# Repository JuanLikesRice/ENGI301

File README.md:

# ENGI301
 Repository for ENGI301 course work

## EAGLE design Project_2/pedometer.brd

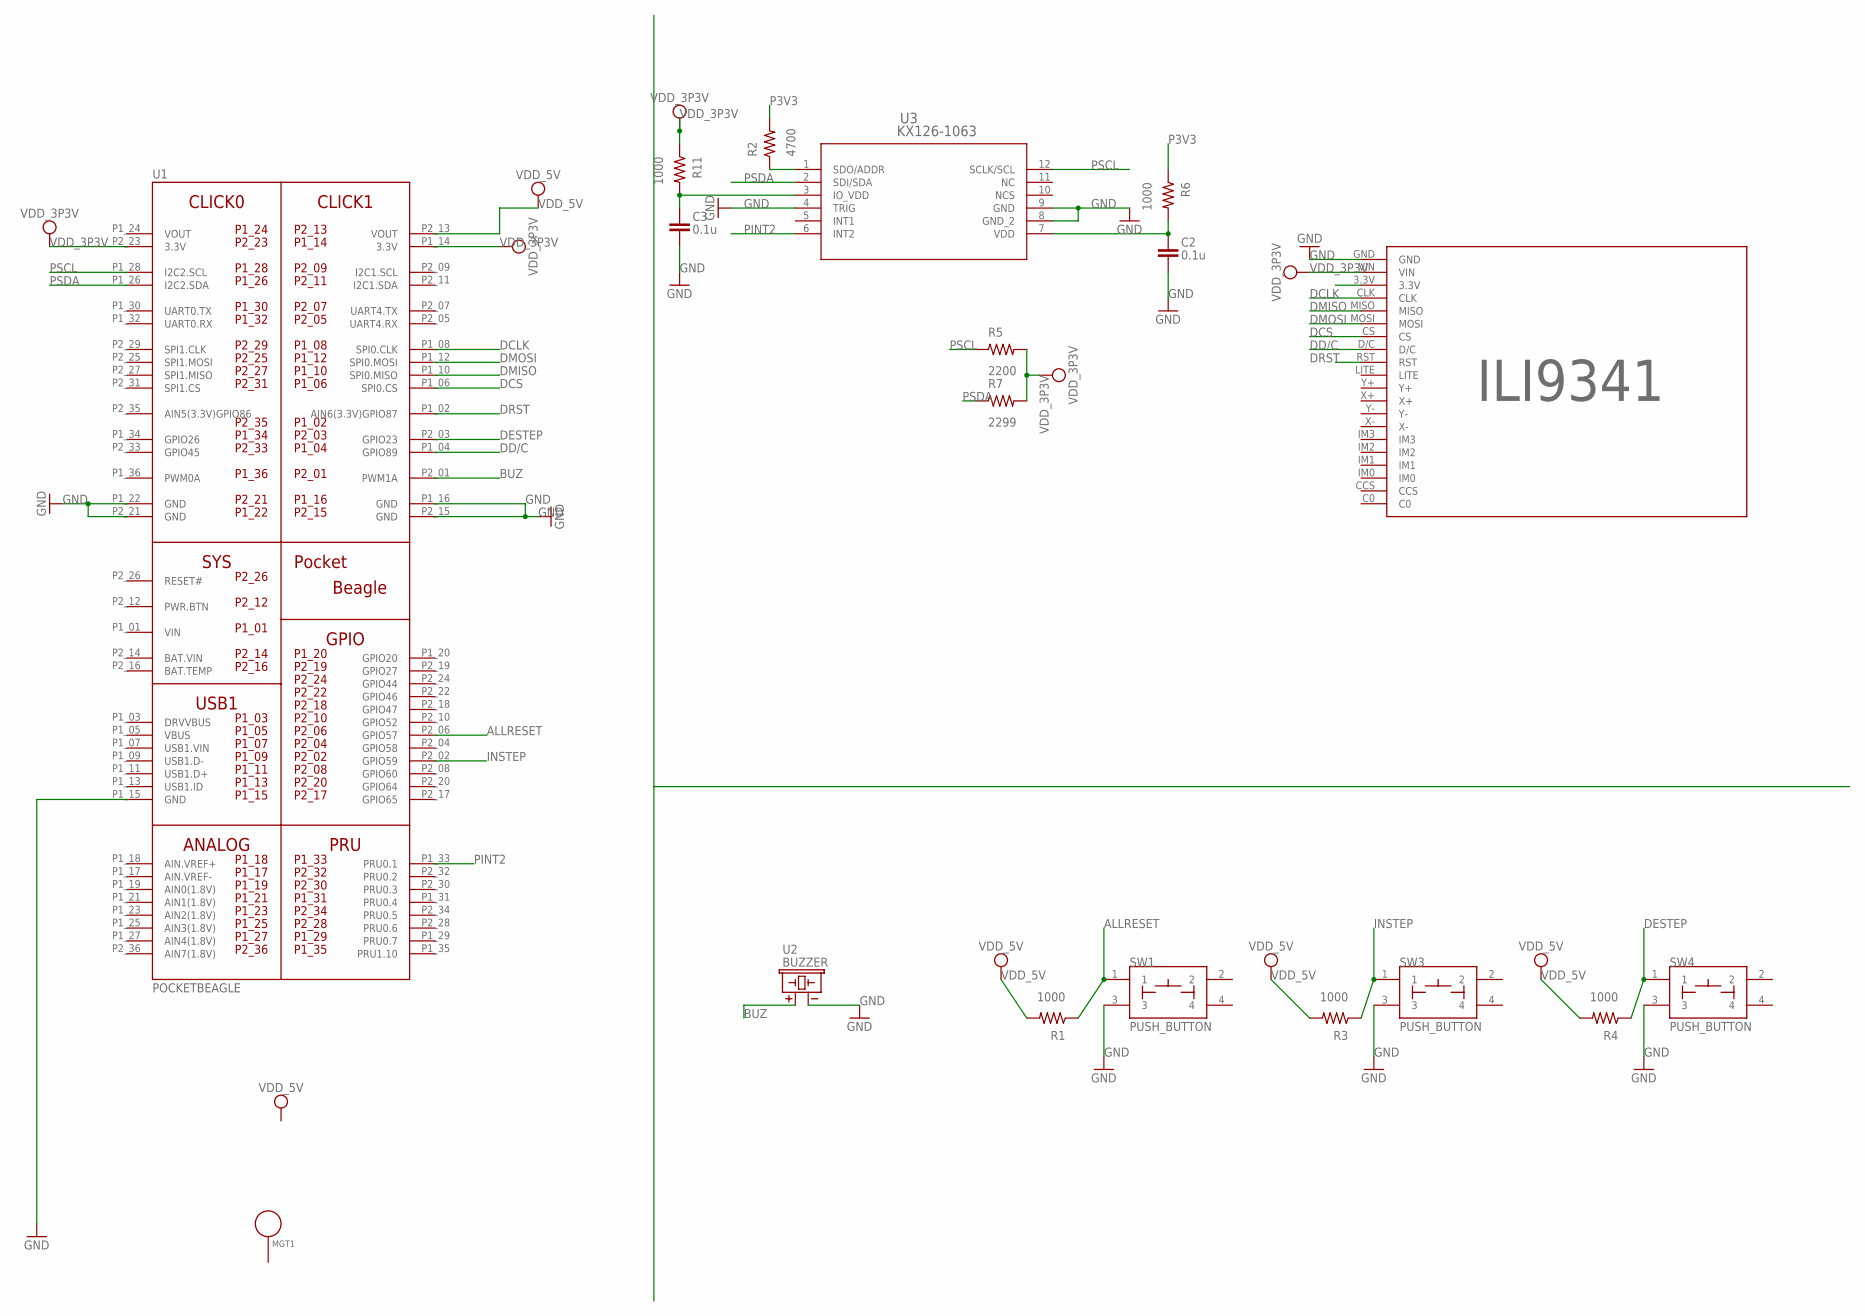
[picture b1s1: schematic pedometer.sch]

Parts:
B2: ILI9341
C2, C3: 0.1u; C0402
MGT1: MOUNTING_HOLE
R1, R3, R4: 1000; R0805
R2: 4700; R0603
R5: 2200; R0603
R6, R11: 1000; R0603
R7: 2299; R0603
SW1, SW3, SW4: PUSH_BUTTON; BUTTON_12.5MM
U1: POCKETBEAGLE
U2: BUZZER; BUZZER_6.5MM
U3: KX126-1063; LGA12_2X2X0P9_KNX

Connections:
ALLRESET: R1.1, SW1.1, U1.P2_06 (GPIO57)
BAT.VIN: U1.P2_14 (BAT.VIN)
BUZ: U1.P2_01 (PWM1A), U2.+
DCLK: B2.CLK, U1.P1_08 (SPI0.CLK)
DCS: B2.CS, U1.P1_06 (SPI0.CS)
DD/C: B2.D/C, U1.P1_04 (GPIO89)
DESTEP: R4.1, SW4.1, U1.P2_03 (GPIO23)
DMISO: B2.MISO, U1.P1_10 (SPI0.MISO)
DMOSI: B2.MOSI, U1.P1_12 (SPI0.MOSI)
DRST: B2.RST, U1.P1_02 (AIN6(3.3V)GPIO87)
GND: B2.GND, C2.2, C3.2, SW1.3, SW3.3, SW4.3, U1.P1_15 (GND), U1.P1_16 (GND), U1.P1_22 (GND), U1.P2_15 (GND), U1.P2_21 (GND), U2.-, U3.4 (TRIG), U3.8 (GND_2), U3.9 (GND)
INSTEP: R3.1, SW3.1, U1.P2_02 (GPIO59)
unnamed: C2.1, R6.2, U3.7 (VDD)
unnamed: C3.1, R11.2, U3.3 (IO_VDD)
unnamed: R2.1, U3.1 (SDO/ADDR)
P3V3: R2.2, R6.1
PINT2: U1.P1_33 (PRU0.1), U3.6 (INT2)
PSCL: R5.1, U1.P1_28 (I2C2.SCL), U3.12 (SCLK/SCL)
PSDA: R7.1, U1.P1_26 (I2C2.SDA), U3.2 (SDI/SDA)
VDD_3P3V: B2.VIN, R5.2, R7.2, R11.1, U1.P1_14 (3.3V), U1.P2_23 (3.3V)
VDD_5V: R1.2, R3.2, R4.2, U1.P2_13 (VOUT)
VIN: U1.P1_01 (VIN)
VOUT: U1.P1_24 (VOUT)

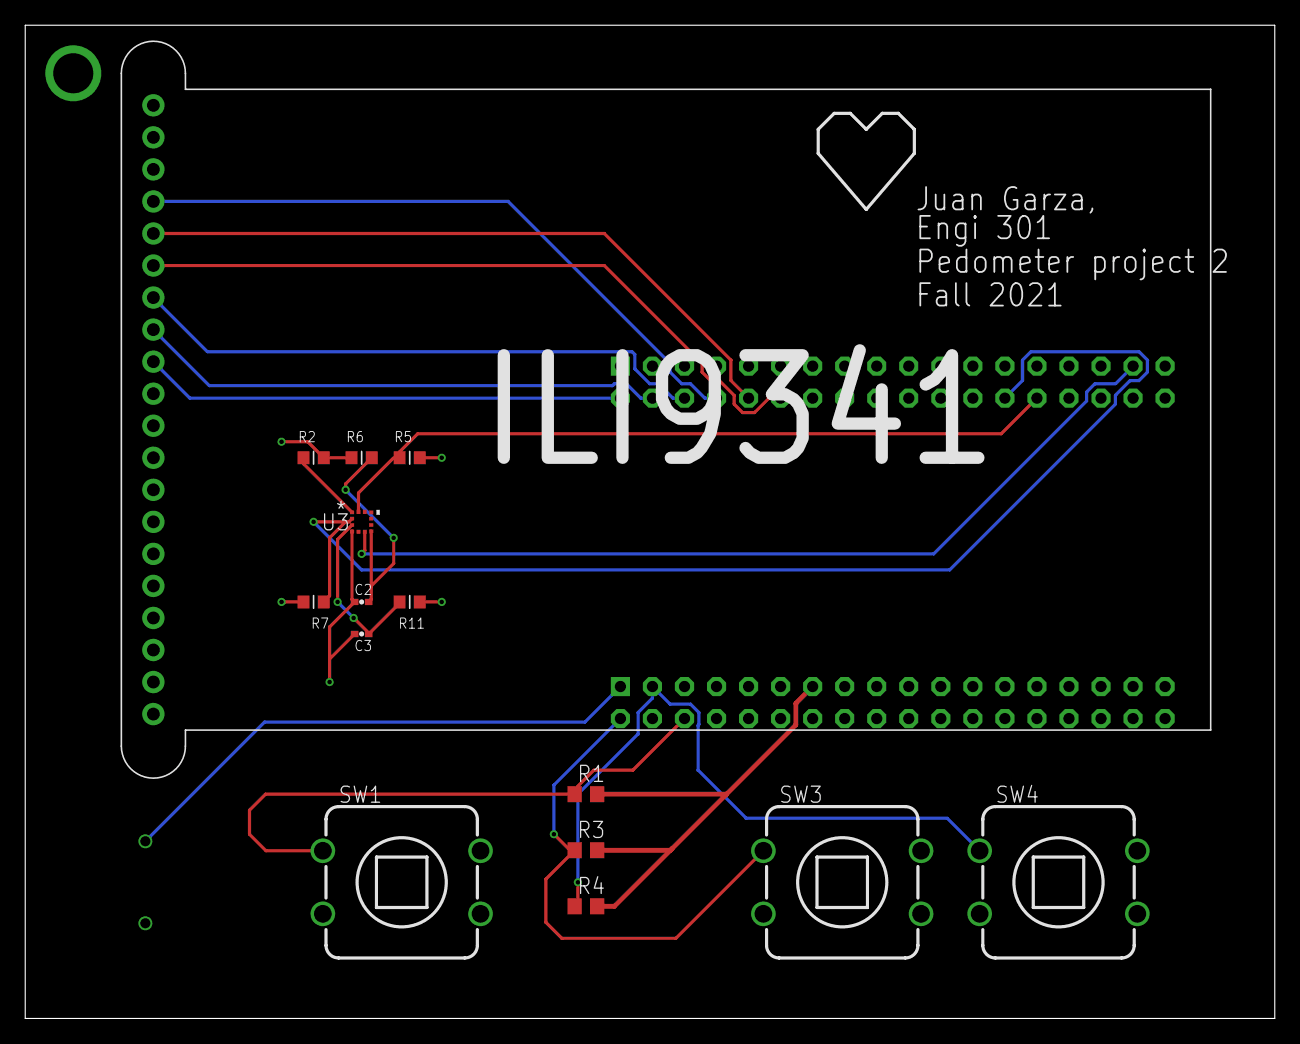
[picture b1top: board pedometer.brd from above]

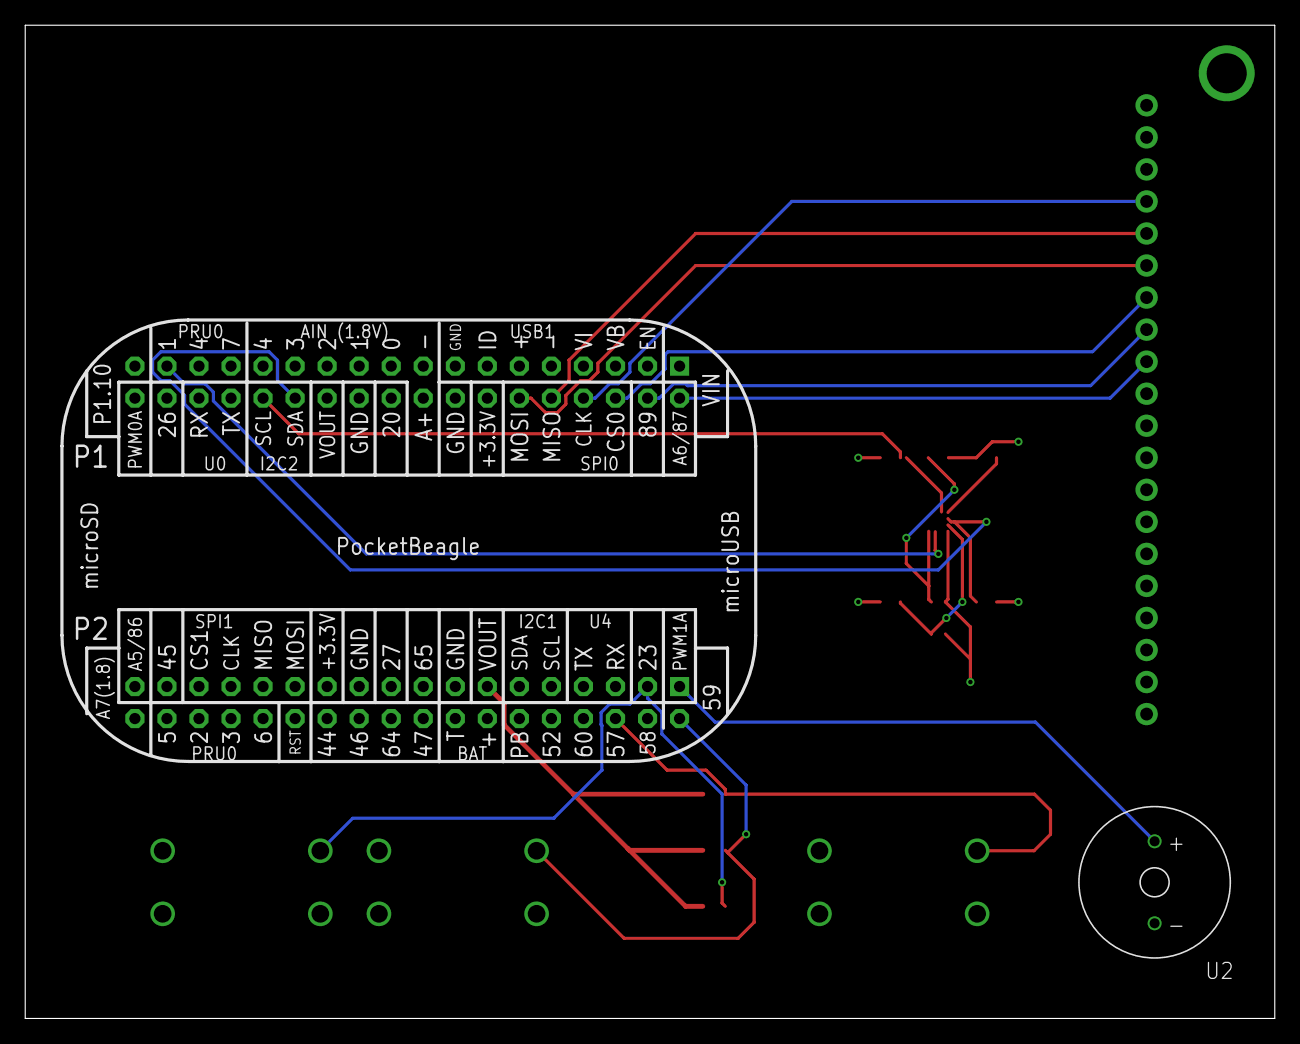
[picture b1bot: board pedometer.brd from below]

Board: 4 copper layers, 99.1 x 78.7 mm, 18 parts (2 on the bottom side), 20 nets.

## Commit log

2021-10-04 Added the assignent recs :)
2021-10-04 It blinks now, yay
2021-10-14 Add files via upload
    Here is my revised proposal
2021-10-15 Garza_ENGI301_project_proposal.pptx
    Here is the file
2021-11-09 Create pedometer
2021-12-15 Create Project_2
2021-12-15 Create Docs

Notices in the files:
parts and their libraries:
COPYRIGHT: Copyright (C) 2021 Ultra Librarian. All rights reserved.
